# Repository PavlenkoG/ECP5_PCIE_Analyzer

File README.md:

# ECP5_PCIE_Analyzer
The main idea of this project is the evaluation of the possibility of using the PCS-Block of ECP5UMG FPGA for PCI-Express protocol analysis.
The PCS Block can deserialize physical PCI-Express signals and decode 8b10b. <p>
Deserialized data can be used to analyze protocol traffic, detecting errors and so on.<p>
The first implementation involves an adapter print to connect PCI-Express lanes to PCS-Block in FPGA and an evaluation board with ECP5UM(G).<p>
The adapter print should be connected to the eval. board through VERSA Expansion headers and SMA-Cables.

https://www.latticesemi.com/products/developmentboardsandkits/ecp5evaluationboard
# VERSA Expansion Headers

# Eval Board top view

# Eval Board bottom view

# PCB

Preparing for applying solder paste

Mounting of SMT Stencil

Applying solder paste

PCB

PCB with solder paste

Mounted PCB

# Python script usage

## record data (on raspberry pi)

```
pi@raspberrypi:~/github/ECP5_PCIE_Analyzer/py_script $ python3 analyzer.py
['analyzer.py']
file removed
Time:  11.82167429399999 s
```

## analyze data

copy data to local
```
scp -r pi@192.168.178.29:~/github/ECP5_PCIE_Analyzer/py_script/*.csv .
```

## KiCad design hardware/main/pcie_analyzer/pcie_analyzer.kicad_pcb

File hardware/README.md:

## Impedance calculation JLCPCB

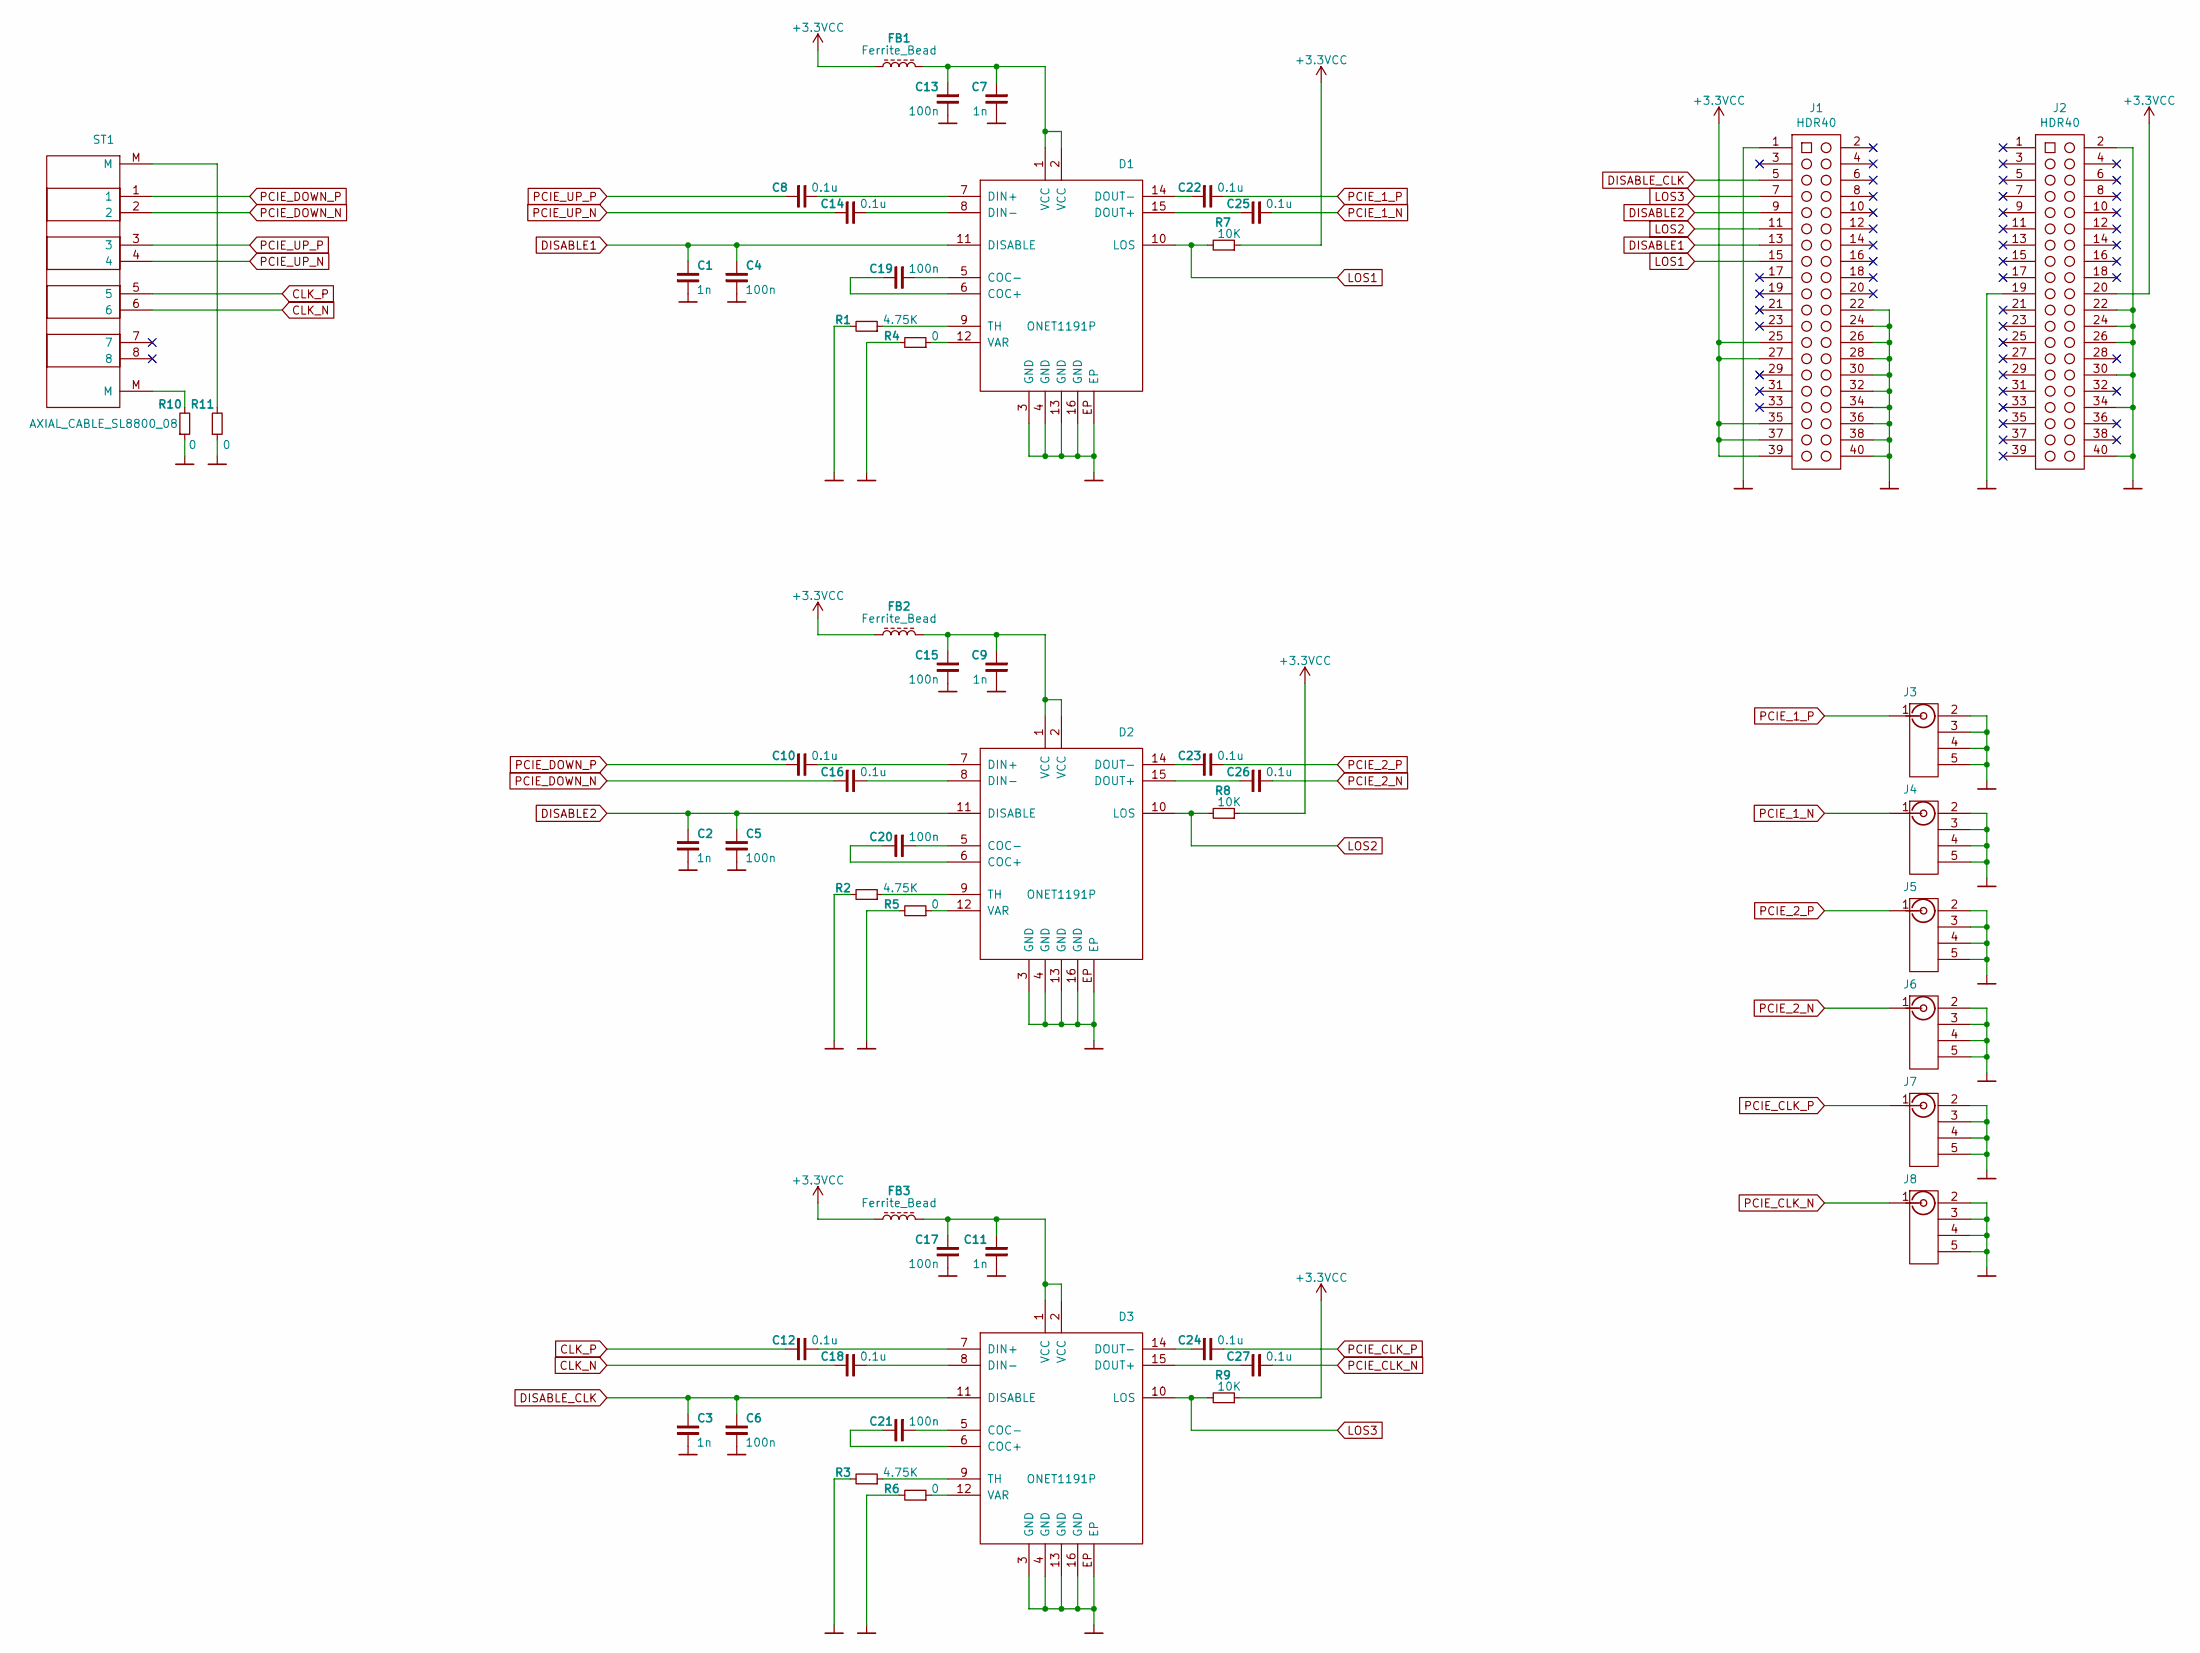
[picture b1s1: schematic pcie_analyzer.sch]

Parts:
C1, C2, C3, C7, C9, C11: 1n; C_0402
C4, C5, C6, C13, C15, C17, C19, C20, C21: 100n; C_0402
C8, C10, C12, C14, C16, C18, C22, C23, C24, C25, C26, C27: 0.1u; C_0402
D1, D2, D3: ONET1191P; VQFN-16
FB1, FB2, FB3: Ferrite_Bead; FB_0402
J1, J2: HDR40; SAMTEC_TSW-120-05-G-D
J3, J4, J5, J6, J7, J8: Conn_Coaxial; SMA_Amphenol_132291_Vertical
R1, R2, R3: 4.75K; R_0402
R4, R5, R6, R10, R11: 0; R_0402
R7, R8, R9: 10K; R_0402
ST1: AXIAL_CABLE_SL8800_08

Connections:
+3.3VCC: FB1.2, FB2.2, FB3.2, J1.25, J1.27, J1.35, J1.37, J1.39, J2.20, R7.2, R8.2, R9.2
CLK_N: C18.2, ST1.6
CLK_P: C12.2, ST1.5
DISABLE1: C1.1, C4.1, D1.11 (DISABLE), J1.13
DISABLE2: C2.1, C5.1, D2.11 (DISABLE), J1.9
DISABLE_CLK: C3.1, C6.1, D3.11 (DISABLE), J1.5
GND: C1.2, C2.2, C3.2, C4.2, C5.2, C6.2, C7.2, C9.2, C11.2, C13.2, C15.2, C17.2, D1.3 (GND), D1.4 (GND), D1.13 (GND), D1.16 (GND), D1.EP, D2.3 (GND), D2.4 (GND), D2.13 (GND), D2.16 (GND), D2.EP, D3.3 (GND), D3.4 (GND), D3.13 (GND), D3.16 (GND), D3.EP, J1.1, J1.22, J1.24, J1.26, J1.28, J1.30, J1.32, J1.34, J1.36, J1.38, J1.40, J2.2, J2.19, J2.22, J2.24, J2.26, J2.30, J2.34, J2.40, J3.2 (Ext), J3.3, J3.4, J3.5, J4.2 (Ext), J4.3, J4.4, J4.5, J5.2 (Ext), J5.3, J5.4, J5.5, J6.2 (Ext), J6.3, J6.4, J6.5, J7.2 (Ext), J7.3, J7.4, J7.5, J8.2 (Ext), J8.3, J8.4, J8.5, R1.1, R2.1, R3.1, R4.1, R5.1, R6.1, R10.2, R11.2
LOS1: D1.10 (LOS), J1.15, R7.1
LOS2: D2.10 (LOS), J1.11, R8.1
LOS3: D3.10 (LOS), J1.7, R9.1
unnamed: C8.1, D1.7 (DIN+)
unnamed: C10.1, D2.7 (DIN+)
unnamed: C11.1, C17.1, D3.1 (VCC), D3.2 (VCC), FB3.1
unnamed: C12.1, D3.7 (DIN+)
unnamed: C7.1, C13.1, D1.1 (VCC), D1.2 (VCC), FB1.1
unnamed: C14.1, D1.8 (DIN-)
unnamed: C9.1, C15.1, D2.1 (VCC), D2.2 (VCC), FB2.1
unnamed: C16.1, D2.8 (DIN-)
unnamed: C18.1, D3.8 (DIN-)
unnamed: C19.1, D1.5 (COC-)
unnamed: C19.2, D1.6 (COC+)
unnamed: C20.1, D2.5 (COC-)
unnamed: C20.2, D2.6 (COC+)
unnamed: C21.1, D3.5 (COC-)
unnamed: C21.2, D3.6 (COC+)
unnamed: C22.2, D1.14 (DOUT-)
unnamed: C23.2, D2.14 (DOUT-)
unnamed: C24.2, D3.14 (DOUT-)
unnamed: C25.2, D1.15 (DOUT+)
unnamed: C26.2, D2.15 (DOUT+)
unnamed: C27.2, D3.15 (DOUT+)
unnamed: D1.9 (TH), R1.2
unnamed: D1.12 (VAR), R4.2
unnamed: D2.9 (TH), R2.2
unnamed: D2.12 (VAR), R5.2
unnamed: D3.9 (TH), R3.2
unnamed: D3.12 (VAR), R6.2
unnamed: R10.1, ST1.M, ST1.M2
unnamed: R11.1, ST1.M, ST1.M1
PCIE_1_N: C25.1, J4.1 (In)
PCIE_1_P: C22.1, J3.1 (In)
PCIE_2_N: C26.1, J6.1 (In)
PCIE_2_P: C23.1, J5.1 (In)
PCIE_CLK_N: C27.1, J8.1 (In)
PCIE_CLK_P: C24.1, J7.1 (In)
PCIE_DOWN_N: C16.2, ST1.2
PCIE_DOWN_P: C10.2, ST1.1
PCIE_UP_N: C14.2, ST1.4
PCIE_UP_P: C8.2, ST1.3

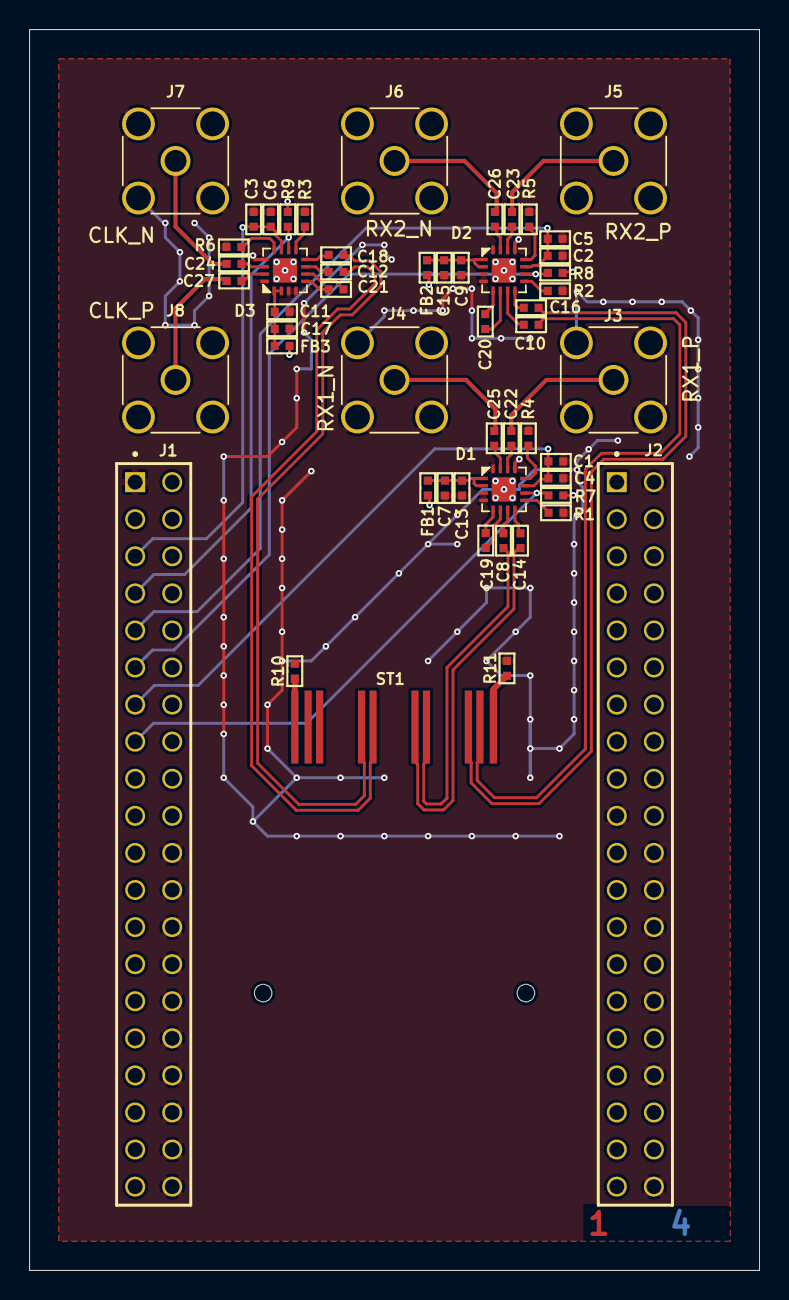
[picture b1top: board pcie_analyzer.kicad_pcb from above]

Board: 4 copper layers, 50.0 x 85.0 mm, 53 parts (0 on the bottom side), 49 nets.

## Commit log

2021-08-06 create KiCad project
2021-08-06 update symbol library
2021-08-06 added op_amp to sch
2021-08-06 doc added
2021-08-06 readme update
2021-08-06 block schema update
2021-08-06 fpga_logic added
2021-08-06 script to desing creating added
2021-08-06 project update
2021-08-06 git ignore update
2021-08-06 vunit update
2021-08-06 vunit, sch work
2021-08-08 add components to library
2021-08-08 library path update
2021-08-08 symbol library update
2021-08-08 schema update
2021-08-12 ferrite bead & ONET1191P added to symbol lib
2021-08-12 schema update, opAmp replaced with ONET1191P
2021-08-12 ferrite bend added to library
2021-08-12 VQFN case added to library
2021-08-12 first annotat schematics,
2021-08-12 pcb added
2021-08-12 project file update
2021-08-13 impedance calculation added to readme
2021-08-13 shema error correction
2021-08-13 dcm update
2021-08-13 placement components
2021-08-13 cache lib update
2021-08-13 vqfn 3d shape added
2021-08-16 pcie twin axial cable added
2021-08-16 readme picture impedance calculation update
2021-08-16 pcb work
2021-08-17 daily work
2021-08-18 sim work
2021-08-19 gitignore update
2021-08-19 axial cable sym and pcb update
2021-08-19 first release sch/pcb
2021-08-19 vunit & top project update
2021-08-19 vunit git ignore update, sim update
2021-08-19 scrambler update
2021-08-19 vunit for activehdl 11 update
2021-08-19 analyzer update
2021-08-19 analyzer_pkg update
2021-08-19 analyzer pkg update
2021-08-20 fpga project work
2021-08-23 fpga readme added
2021-08-23 analyzer daily work
2021-08-23 hardware readme added
2021-08-23 reamde update
2021-08-26 added signals for data/addr interface wathcing
2021-08-26 vunit py cosmetics
2021-08-26 analyzer work
2021-08-26 spi slave added
2021-09-02 assembly plan updated
2021-09-02 make script update
2021-09-02 design work
2021-09-23 ipmlementing top design for ECP Versa
2021-09-23 update readme and upload images
2021-09-23 readme cosmetics
2021-10-07 major design update
2021-10-12 article init
2021-10-12 images added, text work
2021-10-13 images added, article work
2021-10-13 article writing
2022-01-18 doc update
2022-01-18 fpga design update for ECP5UM5G
2022-01-18 testbench update
2022-01-21 second RX channel, reveal analyzer update
2022-01-26 doc and pictures update
2022-01-26 block schema reupload
2022-01-26 tlp filter update
2022-01-26 signal invert disable
2022-01-31 ECP5UM-45caBGA381 symbol added to KiCad library
2022-01-31 daily work, spi controller, tb update
2022-02-01 update analyzer controller
2022-02-01 remove reveal analyzer, implement spi controller
2022-02-01 correct address bus width
2022-02-01 addr width corrected
2022-02-01 constraints - pin 25 mhz input corrected
2022-02-02 spi_slave cs_n output added
2022-02-02 register description added
2022-02-02 controller interface added to package
2022-02-02 controller interface added, wr/rd registers
2022-02-02 spi_controller testbench update
2022-02-03 stim vector file with dcu output added
2022-02-03 signals for data&k from dcu added
2022-02-03 ram default values removed
2022-02-03 spi_controller_tb update - read stim vector file
2022-02-04 init mem to spi test on hardware
2022-02-04 spi freq as variable
2022-02-04 dcu output as textfile for sim
2022-02-04 spi_controller tb update
2022-02-04 vunit activehdl/modelsim select
2022-02-04 increase packets to test whole memory
2022-02-07 analyzer pythons scripts update
2022-02-07 html test output
2022-02-08 vunit run update
2022-02-08 testbench write readed data to file
2022-02-08 read from stim data added
2022-02-08 python script stim files to read
2022-02-09 html update
2022-02-09 parce in/out memory files
2022-02-09 spi read addr error corrected
2022-02-09 html update, classes and functions update
2022-02-09 downstream to file
2022-02-09 raw data to file
2022-02-10 tlp packet, collapse data cell
2022-02-10 font size
2023-10-05 some changes
2023-10-05 build: added pll_200.vhd to project
2023-10-05 refactor(py): format with autopep8
2023-10-05 docs: update readme
2023-10-05 feat: try to parse mem reads/writes
2023-10-06 feat: parse tag
2023-10-06 fix: copy-past error fixed
2023-10-06 feat: use argument for filename
2023-10-06 fix: trigger start resync for downstream added
2023-10-06 feat: parse addr
2023-10-06 feat: parse lower addr
2023-10-06 fix: addr mask
2023-10-06 refactor: correct output length
2023-10-06 feat: parse byte enables
2023-10-06 fix: read stop by rx channel
2023-10-06 feat: parse ts
